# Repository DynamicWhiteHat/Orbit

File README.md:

# Orbit
## An ESP32-powered mini drone with autonomous following capability

## Features:
- ESP32 S3 Wroom 1u SoM
- 4x 0716 coreless motors
- MPU6050 for gyro
- QMC5883 compass
- MS5611 pressure sensor for altitude hold
- 3x SK6812 for signal LEDs
- Battery charging via USB-C
- 2x frame mounted DWM1000 for position tracking
- 1x small form factor DWM1000 board "beacon"
- Firmware based on flix by okalachev, modified to work with this project

## Why I designed this project:
I wanted to design a drone for HackClub's Blueprint program, but not just any regular drone. I wanted to add a feature that would make it stand out, something that would make it unique. So, I decided to give it the ability to autonomously follow you to an accurate degree. After doing some research, I found the DWM1000 modules and decided to design this project. I designed and redesigned the PCBs and CAD for this project many times, with each iteration improving upon the last. This project also gave me the ability to test and improve my PCB and CAD design skills. I understood a lot more about schematic connections while working on this project and learned to route much cleaner traces, even on a compact board.

## Image gallery:
<table align="center">
  <tr>
    <td align="center">
      
    </td>
    <td align="center">
      
    </td>
  </tr>
  <tr>
    <td align="center" colspan="2">
      
    </td>
  </tr>
</table>

## Schematics And PCBS

<details>
<summary>Drone Control Board</summary>
<table align="center">
  <tr>
    <td align="center" colspan="2">
      
    </td>
  </tr>
  <tr>
     <td align="center">
      
    </td>
    <td align="center">
      
    </td>
  </tr>
</table>
</details>

<details>
<summary>Beacon Board</summary>
<table align="center">
  <tr>
    <td align="center" colspan="2">
      
    </td>
  </tr>
  <tr>
     <td align="center">
      
    </td>
    <td align="center">
     
    </td>
  </tr>
</table>
</details>

<details>
<summary>UWB Module Board</summary>
<table align="center">
  <tr>
    <td align="center" colspan="2">
      
  </tr>
  <tr>
     <td align="center">
      
    </td>
    <td align="center">
      
    </td>
  </tr>
</table>
</details>

## How It Works

The drone is powered by a custom designed PCB based on the ESP-32 S3 Wroom 1u SoM. It includes three SK6812 mini-e LEDs to serve as a status signal, located at the rear of the drone. There are three sensors located on board to help with flight. The MPU-6050 is a triple-axis accelerometer and gyroscope that is essential to help the drone fly. The MS5611 is a pressure sensor that is used to record and maintain height during flight. The final sensor, an HMC5883, is a triple-axis magnetometer that is used to report the drone's heading. The latter two sensors are reported in QGroundControl or any other flight operating station to provide information to the controller. The 0716 coreless motors are powered by a simple MOSFET circuit, designed by MaxImagination. This circuit has a small footprint and fits great for small projects, such as this drone. Autonomous flight is achieved using two DWM1000 modules mounted on the sides of the drone. These were implemented on the main PCB using 10-pin JSTs to allow modular connectivity, allowing the controller to select whether to fly with or without the ranging sensors. The DWM1000s mounted on the drone communicate with an external DWM1000 "beacon" that is with the controller or person of interest. This beacon is encased in a watch case to make it easy to wear. By sending messages between the modules, the distance between them can be calculated, allowing the beacon's location to be triangulated. This location is then set in the PID controllers, allowing the drone to autonomously navigate.

## Bill Of Materials

| Item          | Description        | Quantity             | URL                                                                                 | Unit Price ($) | Total Price ($) |
|---------------|--------------------|----------------------|-------------------------------------------------------------------------------------|----------------|-----------------|
| DWM1000       | Ranging Modules    | 3                    | https://www.aliexpress.us/item/3256808347510093.html                                | $15.13         | $50.90          |
| XIAO ESP-32   | For Beacon         | 1                    | Already Have                                                                        |                |                 |
| LCSC          | PCB Components     | 1 Order of All Parts | See LCSC BOM                                                                        |                | $36.92          |
| JST Connector | For DWM Connection | 1 Pack of 10         | https://www.aliexpress.us/item/3256805775471278.html                                | $3.09          | $3.09           |
| Battery       | For Beacon         | 1                    | https://www.amazon.com/AKZYTUE-Battery-Rechargeable-Lithium-Connector/dp/B07TXJ4C46 | $7.79          | $7.79           |
| Battery       | For Drone          | 1                    | https://www.amazon.com/EEMB-Battery-Rechargeable-Lithium-Connector/dp/B0B7R8CS2C    | $6.99          | $7.99           |
| Motors        | For Drone          | 1 Pack of 4          | https://www.amazon.com/Coliao-Coreless-19000KV-Propeller-Quadcopter/dp/B0CHYDJMF2/  | $10            | $11             |
| Antenna       | For Drone          | 1                    | https://www.aliexpress.us/item/3256806233080373.html                                | $1.64          | $1.64           |
| Screws        | To Hold Case       | 1 Pack               | https://www.aliexpress.us/item/3256806233080373.html                                | $5.90          | $5.90           |
| JLCPCB Order  | PCBs               | 1                    | JLCPCB Quote                                                                        | $17.16          | $17.16           |
|               |                    |                      |                                                                                     |                | $139.08         |

### LCSC Bill Of Materials
| Description                                                                                 | Quantity Needed | Mrf#                    | Minimum Order Qty. | Unit Price(USD) | Ext.Price(USD) | LCSC#     | Product Link                                       |
|---------------------------------------------------------------------------------------------|-----------------|-------------------------|------------|-----------------|----------------|-----------|----------------------------------------------------|
| N-Channel 20V 4A 1.2W Surface Mount SOT-23                                                  | 4               | SI2300                  | 20         | 0.0164          | 0.33           | C5224175  | https://www.lcsc.com/product-detail/C5224175.html  |
| QFN-24-EP(4x4) Accelerometers RoHS                                                          | 1               | MPU-6050                | 1          | 6.8489          | 6.85           | C24112    | https://www.lcsc.com/product-detail/C24112.html    |
| 1Kpa~1.2bar QFN-8(3x5) Pressure Sensors, Transducers RoHS                                   | 1               | MS561101BA03-50         | 1          | 5.5485          | 5.55           | C15639    | https://www.lcsc.com/product-detail/C15639.html    |
| I2C LGA-16(3x3) Linear, Compass (ICs) RoHS                                                  | 1               | QMC5883P                | 1          | 1.4485          | 1.45           | C2847467  | https://www.lcsc.com/product-detail/C2847467.html  |
| Red LED Indication - Discrete 2.7V~3.2V 0602                                                | 5               | YLED0603R               | 200        | 0.0055          | 0.55           | C19171390 | https://www.lcsc.com/product-detail/C19171390.html |
| Emerald Green LED Indication - Discrete 2.7V~3.2V 0603                                      | 13             | YLED0603G               | 200        | 0.0054          | 1.08           | C19273151 | https://www.lcsc.com/product-detail/C19273151.html |
| 2.4GHz ESP32-S3R8 -98.2dBm SMD,19.2x18mm RF Transceiver Modules and Modems RoHS             | 1               | ESP32-S3-WROOM-1U-N16R8 | 1          | 5.3260          | 5.33           | C3013946  | https://www.lcsc.com/product-detail/C3013946.html  |
| 100nF ±10% 50V Ceramic Capacitor X7R 0603                                                   | 17              | CC0603KRX7R9BB104       | 100        | 0.0025          | 0.25           | C14663    | https://www.lcsc.com/product-detail/C14663.html    |
| 220nF ±10% 50V Ceramic Capacitor X7R 0603                                                   | 1               | CL10B224KB8NNNC         | 100        | 0.0081          | 0.81           | C64705    | https://www.lcsc.com/product-detail/C64705.html    |
| 4.7uF ±10% 10V Ceramic Capacitor X5R 0603                                                   | 3               | CL10A475KP8NNNC         | 50         | 0.0051          | 0.26           | C1705     | https://www.lcsc.com/product-detail/C1705.html     |
| 10uF ±10% 10V Ceramic Capacitor X5R 0603                                                    | 17              | CL10A106KP8NNNC         | 50         | 0.0058          | 0.29           | C19702    | https://www.lcsc.com/product-detail/C19702.html    |
| 1uF ±10% 50V Ceramic Capacitor X5R 0603                                                     | 1               | CL10A105KB8NNNC         | 50         | 0.0049          | 0.25           | C15849    | https://www.lcsc.com/product-detail/C15849.html    |
| 10nF ±10% 50V Ceramic Capacitor X7R 0603                                                    | 2               | CC0603KRX7R9BB103       | 100        | 0.0022          | 0.22           | C100042   | https://www.lcsc.com/product-detail/C100042.html   |
| Diode Independent 100V 300mA Surface Mount SOD-123                                          | 4               | 1N4148W                 | 100        | 0.0056          | 0.56           | C917030   | https://www.lcsc.com/product-detail/C917030.html   |
| Diode Array 1 Pair Common Cathode 30V 200mA Surface Mount SOT-23                            | 1               | BAT54C                  | 50         | 0.0063          | 0.32           | C916424   | https://www.lcsc.com/product-detail/C916424.html   |
| Diode 40V 1A Surface Mount SOD-123                                                          | 1               | 1N5819HW                | 20         | 0.0237          | 0.47           | C5439970  | https://www.lcsc.com/product-detail/C5439970.html  |
| USB-C (USB TYPE-C) Receptacle Connector 16 Position Surface Mount                           | 1               | TYPE-C-31-M-12          | 5          | 0.1762          | 0.88           | C165948   | https://www.lcsc.com/product-detail/C165948.html   |
| 100mW 10kΩ 75V ±100ppm/℃ Thick Film Resistor ±1% 0603 Chip Resistor - Surface Mount RoHS    | 14              | RC0603FR-0710KL         | 100        | 0.0011          | 0.11           | C98220    | https://www.lcsc.com/product-detail/C98220.html    |
| 5.1kΩ ±1% 100mW 0603 Thick Film Resistor                                                    | 2               | FRC0603F5101TS          | 100        | 0.0009          | 0.09           | C2907044  | https://www.lcsc.com/product-detail/C2907044.html  |
| 400mΩ ±1% 100mW 0603 Thick Film Resistor                                                    | 1               | FRL0603FR400TS          | 100        | 0.0033          | 0.33           | C5126047  | https://www.lcsc.com/product-detail/C5126047.html  |
| 1kΩ ±1% 100mW 0603 Thick Film Resistor                                                      | 10              | FRC0603F1001TS          | 100        | 0.0009          | 0.09           | C2907002  | https://www.lcsc.com/product-detail/C2907002.html  |
| 5kΩ 100mW 75V ±50ppm/℃ Thin Film Resistor ±0.1% 0603 Chip Resistor - Surface Mount RoHS     | 1               | RT0603BRE075KL          | 50         | 0.0172          | 0.86           | C862232   | https://www.lcsc.com/product-detail/C862232.html   |
| 100mW 1MΩ 75V ±100ppm/℃ Thick Film Resistor ±1% 0603 Chip Resistor - Surface Mount RoHS     | 5               | RC0603FR-071ML          | 100        | 0.0012          | 0.12           | C105578   | https://www.lcsc.com/product-detail/C105578.html   |
| Tactile Switch SPST 160gf 2mm SMD (SMT) Tab 4mm x 3mm Surface Mount                         | 2               | TS-1088-AR02016         | 10         | 0.0423          | 0.42           | C720477   | https://www.lcsc.com/product-detail/C720477.html   |
| Lithium Battery 1A ESOP-8 Battery Management RoHS                                           | 1               | TP4056-42-ESOP8         | 5          | 0.1784          | 0.89           | C16581    | https://www.lcsc.com/product-detail/C16581.html    |
| Positive Fixed 3.3V SOT-223 Voltage Regulators - Linear, Low Drop Out (LDO) Regulators RoHS | 5               | AP7361C-33E-13          | 5          | 0.2462          | 1.23           | C500795   | https://www.lcsc.com/product-detail/C500795.html   |
| 220kΩ ±1% 100mW 0603 Thick Film Resistor                                                    | 2               | FRC0603F2203TS          | 100        | 0.0010          | 0.10           | C2907013  | https://www.lcsc.com/product-detail/C2907013.html  |
| 470Ω ±1% 100mW 0603 Thick Film Resistor                                                     | 12              | 0603WAF4700T5E          | 100        | 0.0012          | 0.12           | C23179    | https://www.lcsc.com/product-detail/C23179.html    |
| Slide Switch SPDT 300mA @ 5V Surface Mount, Right Angle Rectangular Columnar                | 1               | SSSS811101              | 5          | 0.1408          | 0.70           | C109335   | https://www.lcsc.com/product-detail/C109335.html   |
| Connector Header 2 position 2mm Pitch 2A Right Angle -25℃~+85℃                            | 1               | S2B-PH-K-S(LF)(SN)      | 20         | 0.0351          | 0.70           | C17375    | https://lcsc.com/product-detail/C17375             |

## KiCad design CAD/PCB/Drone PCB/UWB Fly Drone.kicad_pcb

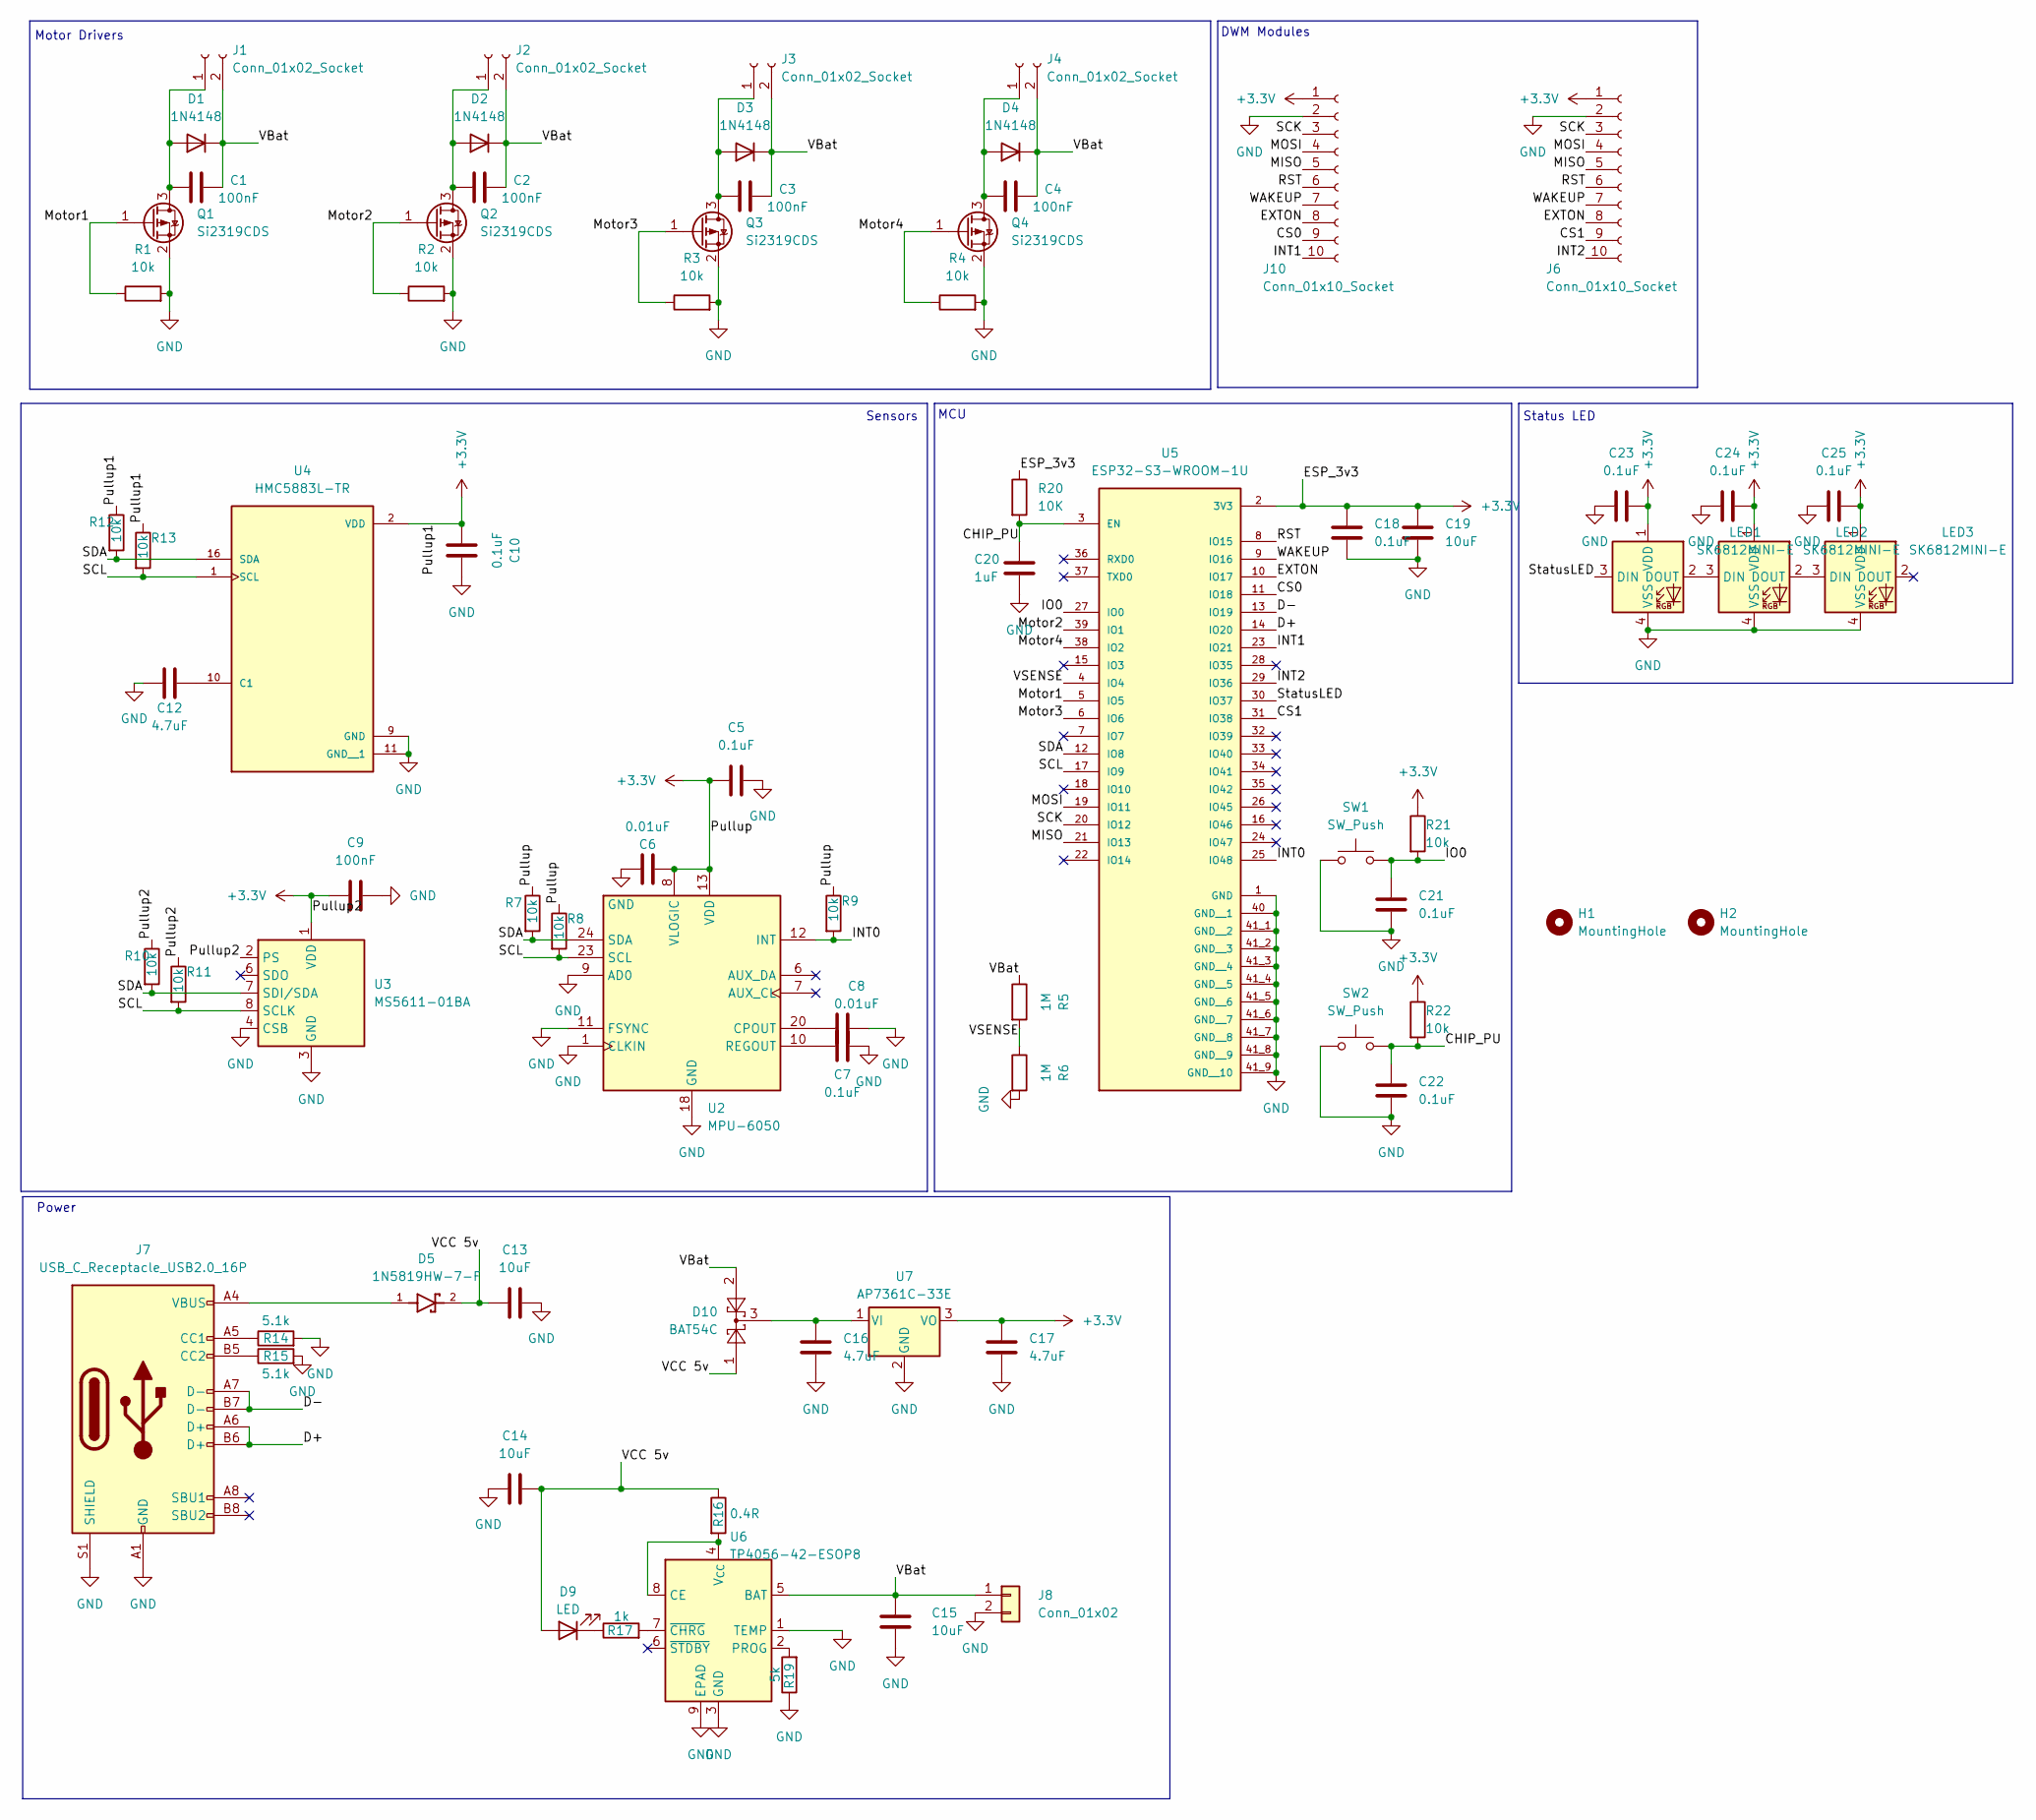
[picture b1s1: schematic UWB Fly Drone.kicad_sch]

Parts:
C1, C2, C3, C4, C9: 100nF; C_0603_1608Metric
C5, C7, C10, C18, C21, C22, C23, C24, C25: 0.1uF; C_0603_1608Metric
C6, C8: 0.01uF; C_0603_1608Metric
C12, C16, C17: 4.7uF; C_0603_1608Metric
C13, C14, C15, C19: 10uF; C_0603_1608Metric
C20: 1uF; C_0603_1608Metric
D1, D2, D3, D4: 1N4148; D_SOD-123
D5: 1N5819HW-7-F; D_SOD-123; PARTREV 18-2
D9: LED; LED_0603_1608Metric
D10: BAT54C; SOT-23
H1, H2: MountingHole; MountingHole_2.2mm_M2
J1, J2, J3, J4: Conn_01x02_Socket; SolderWire-0.5sqmm_1x02_P4.8mm_D0.9mm_OD2.3mm
J6, J10: Conn_01x10_Socket; JST_PH_S10B-PH-K_1x10_P2.00mm_Horizontal
J7: USB_C_Receptacle_USB2.0_16P; USB_C_Receptacle_HRO_TYPE-C-31-M-12
J8: Conn_01x02; JST_PH_S2B-PH-K_1x02_P2.00mm_Horizontal
LED1, LED2, LED3: SK6812MINI-E; LED_6028R
Q1, Q2, Q3, Q4: Si2319CDS; SOT-23
R1, R2, R3, R4, R7, R8, R9, R10, R11, R12, R13, R21, R22: 10k; R_0603_1608Metric
R5, R6: 1M; R_0603_1608Metric
R14, R15: 5.1k; R_0603_1608Metric
R16: 0.4R; R_0603_1608Metric
R17: 1k; R_0603_1608Metric
R19: 5k; R_0603_1608Metric
R20: 10K; R_0603_1608Metric
SW1, SW2: SW_Push; SW_TS-1088-AR02016
U2: MPU-6050; InvenSense_QFN-24_4x4mm_P0.5mm
U3: MS5611-01BA; LGA-8_3x5mm_P1.25mm
U4: HMC5883L-TR; XDCR_HMC5883L-TR; PARTREV E
U5: ESP32-S3-WROOM-1U; XCVR_ESP32-S3-WROOM-1U; PARTREV v0.6
U6: TP4056-42-ESOP8; SOIC-8-1EP_3.9x4.9mm_P1.27mm_EP2.41x3.3mm_ThermalVias
U7: AP7361C-33E; SOT-223-3_TabPin2

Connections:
+3.3V: C5.1, C6.1, C9.1, C10.1, C17.1, C18.1, C19.1, C23.2, C24.2, C25.2, J6.1, J10.1, LED1.1 (VDD), LED2.1 (VDD), LED3.1 (VDD), R7.1, R8.1, R9.1, R10.1, R11.1, R12.1, R13.1, R20.1, R21.1, R22.1, U2.8 (VLOGIC), U2.13 (VDD), U3.1 (VDD), U3.2 (PS), U4.2 (VDD), U5.2 (3V3), U7.3 (VO)
/CHIP_PU: C20.1, C22.1, R20.2, R22.2, SW2.2, U5.3 (EN)
/CS0: J10.9, U5.11 (IO18)
/CS1: J6.9, U5.31 (IO38)
/D+: J7.A6 (D+), J7.B6 (D+), U5.14 (IO20)
/D-: J7.A7 (D-), J7.B7 (D-), U5.13 (IO19)
/EXTON: J6.8, J10.8, U5.10 (IO17)
/INT0: R9.2, U2.12 (INT), U5.25 (IO48)
/INT1: J10.10, U5.23 (IO21)
/INT2: J6.10, U5.29 (IO36)
/IO0: C21.1, R21.2, SW1.2, U5.27 (IO0)
/MISO: J6.5, J10.5, U5.21 (IO13)
/MOSI: J6.4, J10.4, U5.19 (IO11)
/Motor1: Q1.1 (G), R1.1, U5.5 (IO5)
/Motor2: Q2.1 (G), R2.1, U5.39 (IO1)
/Motor3: Q3.1 (G), R3.1, U5.6 (IO6)
/Motor4: Q4.1 (G), R4.1, U5.38 (IO2)
/RST: J6.6, J10.6, U5.8 (IO15)
/SCK: J6.3, J10.3, U5.20 (IO12)
/SCL: R8.2, R11.2, R13.2, U2.23 (SCL), U3.8 (SCLK), U4.1 (SCL), U5.17 (IO9)
/SDA: R7.2, R10.2, R12.2, U2.24 (SDA), U3.7 (SDI/SDA), U4.16 (SDA), U5.12 (IO8)
/StatusLED: LED1.3 (DIN), U5.30 (IO37)
/VBat: C1.2, C2.2, C3.2, C4.2, C15.1, D1.1 (K), D2.1 (K), D3.1 (K), D4.1 (K), D10.2, J1.2, J2.2, J3.2, J4.2, J8.1, R5.1, U6.5 (BAT)
/VCC 5v: C13.1, C14.2, D5.2, D9.2 (A), D10.1, R16.1
/VSENSE: R5.2, R6.1, U5.4 (IO4)
/WAKEUP: J6.7, J10.7, U5.9 (IO16)
GND: C5.2, C6.2, C7.2, C8.2, C9.2, C10.2, C12.1, C13.2, C14.1, C15.2, C16.2, C17.2, C18.2, C19.2, C20.2, C21.2, C22.2, C23.1, C24.1, C25.1, J6.2, J7.A1 (GND), J7.A12 (GND), J7.B1 (GND), J7.B12 (GND), J7.S1 (SHIELD), J8.2, J10.2, LED1.4 (VSS), LED2.4 (VSS), LED3.4 (VSS), Q1.2 (S), Q2.2 (S), Q3.2 (S), Q4.2 (S), R1.2, R2.2, R3.2, R4.2, R6.2, R14.2, R15.2, R19.1, SW1.1, SW2.1, U2.1 (CLKIN), U2.9 (AD0), U2.11 (FSYNC), U2.18 (GND), U3.3 (GND), U3.4 (CSB), U3.5 (CSB), U4.9 (GND), U4.11 (GND__1), U5.1 (GND), U5.40 (GND__1), U5.41_1 (GND__2), U5.41_2 (GND__3), U5.41_3 (GND__4), U5.41_4 (GND__5), U5.41_5 (GND__6), U5.41_6 (GND__7), U5.41_7 (GND__8), U5.41_8 (GND__9), U5.41_9 (GND__10), U6.1 (TEMP), U6.3 (GND), U6.9 (EPAD), U7.2 (GND)
unnamed: C1.1, D1.2 (A), J1.1, Q1.3 (D)
unnamed: C2.1, D2.2 (A), J2.1, Q2.3 (D)
unnamed: C3.1, D3.2 (A), J3.1, Q3.3 (D)
unnamed: C4.1, D4.2 (A), J4.1, Q4.3 (D)
unnamed: D5.1, J7.A4 (VBUS), J7.A9 (VBUS), J7.B4 (VBUS), J7.B9 (VBUS)
unnamed: D9.1 (K), R17.1
unnamed: J7.A5 (CC1), R14.1
unnamed: J7.B5 (CC2), R15.1
unnamed: LED1.2 (DOUT), LED2.3 (DIN)
unnamed: LED2.2 (DOUT), LED3.3 (DIN)
unnamed: C8.1, U2.20 (CPOUT)
unnamed: C7.1, U2.10 (REGOUT)
unnamed: C12.2, U4.10 (C1)
unnamed: R16.2, U6.4 (V_{CC}), U6.8 (CE)
unnamed: R19.2, U6.2 (PROG)
unnamed: R17.2, U6.7 (~CHRG)
unnamed: C16.1, D10.3, U7.1 (VI)

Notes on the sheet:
Status LED
MCU
Motor Drivers
DWM Modules
Power
Sensors

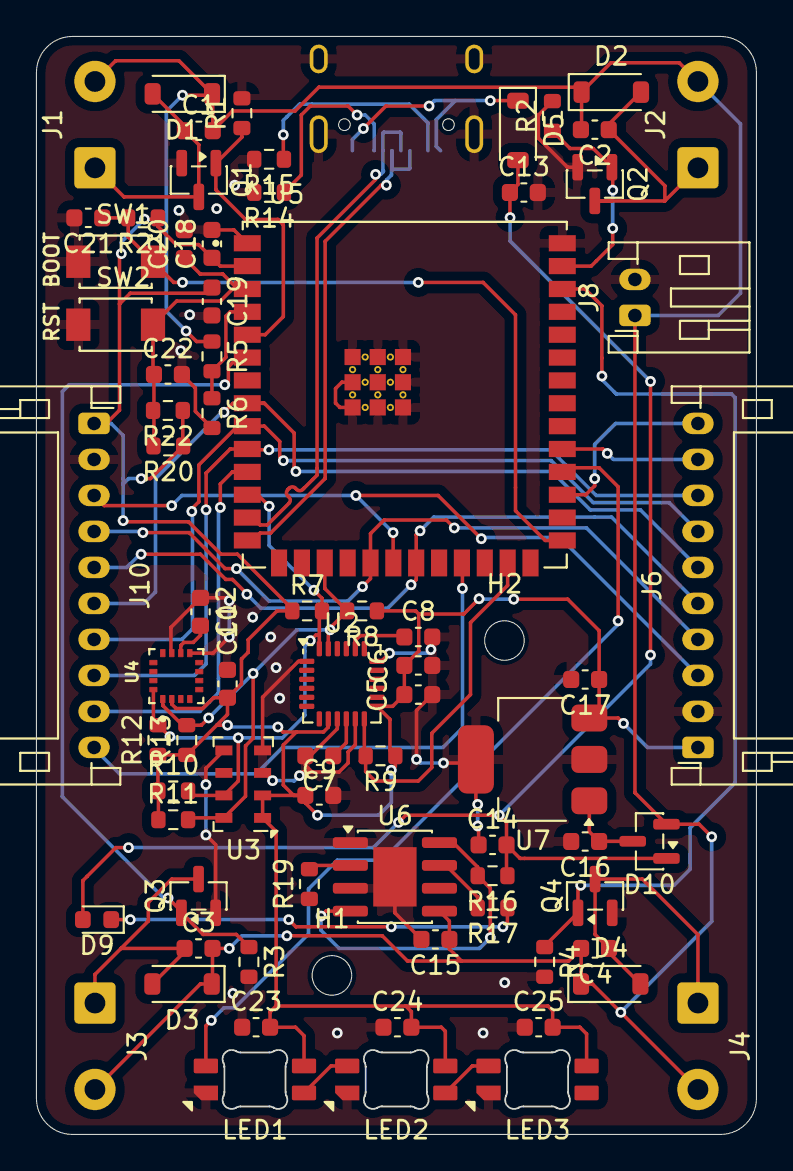
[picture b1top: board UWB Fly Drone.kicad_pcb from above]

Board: 2 copper layers, 39.9 x 61.0 mm, 77 parts (1 on the bottom side), 44 nets.

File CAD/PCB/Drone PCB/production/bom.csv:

Designator,Footprint,Quantity,Value,LCSC Part #
"C1, C2, C3, C4, C9",0603,5,100nF,
"C10, C18, C21, C22, C23, C24, C25, C5, C7",0603,9,0.1uF,
"C12, C16, C17",0603,3,4.7uF,
"C13, C14, C15, C19",0603,4,10uF,
C20,0603,1,1uF,
"C6, C8",0603,2,0.01uF,
"D1, D2, D3, D4",D_SOD-123,4,1N4148,
D10,SOT-23,1,BAT54C,
D5,D_SOD-123,1,1N5819HW-7-F,
D9,0603,1,LED,
"J1, J2, J3, J4",SolderWire-0.5sqmm_1x02_P4.8mm_D0.9mm_OD2.3mm,4,Conn_01x02_Socket,
"J10, J6",JST_PH_S10B-PH-K_1x10_P2.00mm_Horizontal,2,Conn_01x10_Socket,
J7,USB_C_Receptacle_HRO_TYPE-C-31-M-12,1,USB_C_Receptacle_USB2.0_16P,
J8,JST_PH_S2B-PH-K_1x02_P2.00mm_Horizontal,1,Conn_01x02,
"LED1, LED2, LED3",LED_6028R,3,SK6812MINI-E,
"Q1, Q2, Q3, Q4",SOT-23,4,Si2319CDS,
"R1, R10, R11, R12, R13, R2, R20, R21, R22, R3, R4, R7, R8, R9",0603,14,10k,
"R14, R15",0603,2,5.1k,
R16,0603,1,0.4R,
R17,0603,1,1k,
R19,0603,1,5k,
"R5, R6",0603,2,1M,
"SW1, SW2",SW_TS-1088-AR02016,2,SW_Push,
U2,InvenSense_QFN-24_4x4mm_P0.5mm,1,MPU-6050,
U3,LGA-8_3x5mm_P1.25mm,1,MS5611-01BA,
U4,XDCR_HMC5883L-TR,1,HMC5883L-TR,
U5,XCVR_ESP32-S3-WROOM-1U,1,ESP32-S3-WROOM-1U,
U6,SOIC-8-1EP_3.9x4.9mm_P1.27mm_EP2.41x3.3mm_ThermalVias,1,TP4056-42-ESOP8,
U7,SOT-223-3_TabPin2,1,AP7361C-33E,

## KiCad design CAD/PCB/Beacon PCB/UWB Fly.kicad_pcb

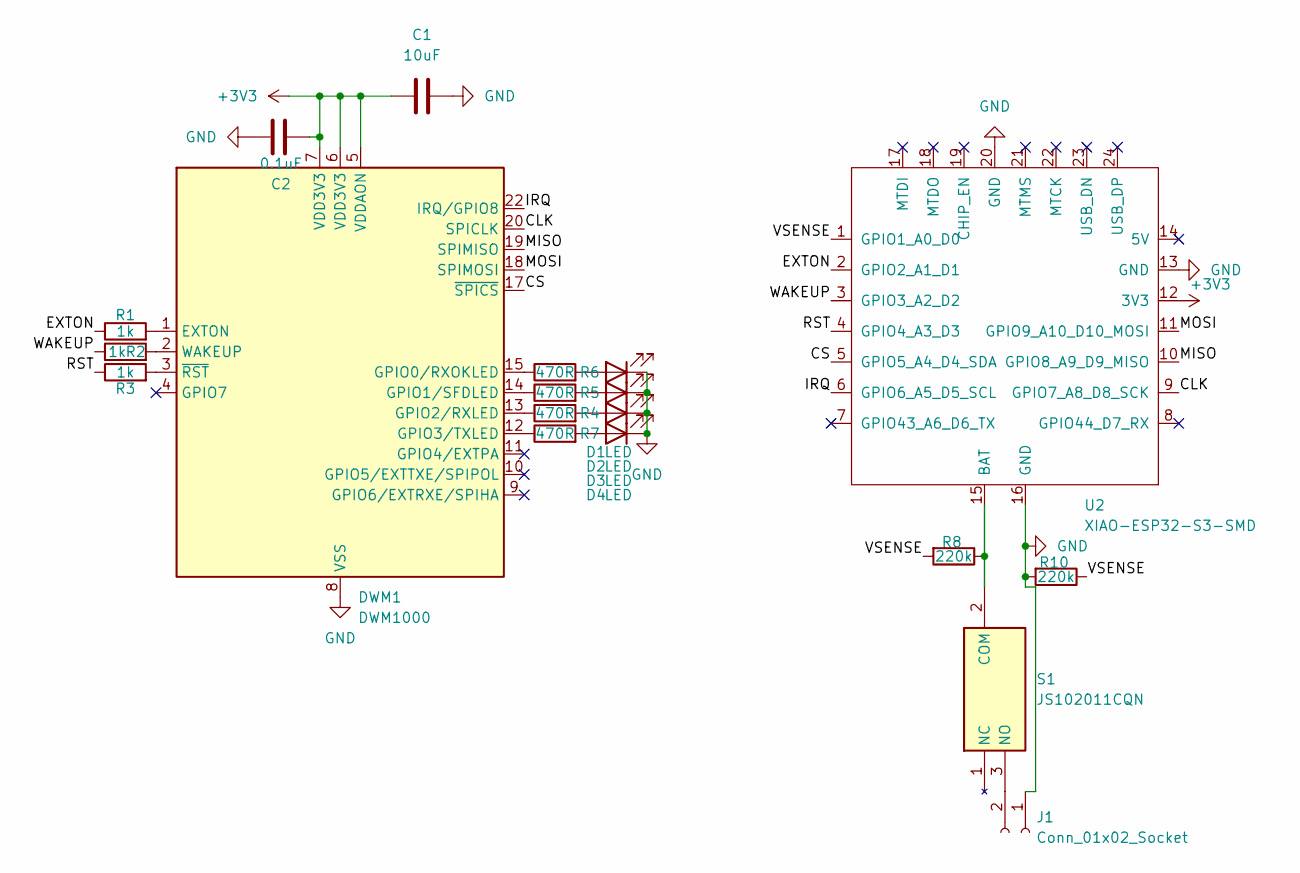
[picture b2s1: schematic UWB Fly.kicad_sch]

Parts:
C1: 10uF; C_0603_1608Metric
C2: 0.1uF; C_0603_1608Metric
D1, D2, D3, D4: LED; LED_0603_1608Metric
DWM1: DWM1000
J1: Conn_01x02_Socket; SolderWire-0.5sqmm_1x02_P4.8mm_D0.9mm_OD2.3mm
R1, R2, R3: 1k; R_0603_1608Metric
R4, R5, R6, R7: 470R; R_0603_1608Metric
R8, R10: 220k; R_0603_1608Metric
S1: JS102011CQN; SW_SSSS811101; Mouser Part Number 611-JS102011CQN
U2: XIAO-ESP32-S3-SMD; XIAO-ESP32S3-SMD

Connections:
+3V3: C1.1, C2.1, DWM1.5 (VDDAON), DWM1.6 (VDD3V3), DWM1.7 (VDD3V3), U2.12 (3V3)
/CLK: DWM1.20 (SPICLK), U2.9 (GPIO7_A8_D8_SCK)
/CS: DWM1.17 (~SPICS), U2.5 (GPIO5_A4_D4_SDA)
/EXTON: R1.1, U2.2 (GPIO2_A1_D1)
/IRQ: DWM1.22 (IRQ/GPIO8), U2.6 (GPIO6_A5_D5_SCL)
/MISO: DWM1.19 (SPIMISO), U2.10 (GPIO8_A9_D9_MISO)
/MOSI: DWM1.18 (SPIMOSI), U2.11 (GPIO9_A10_D10_MOSI)
/RST: R3.1, U2.4 (GPIO4_A3_D3)
/VSENSE: R8.2, R10.1, U2.1 (GPIO1_A0_D0)
/WAKEUP: R2.1, U2.3 (GPIO3_A2_D2)
GND: C1.2, C2.2, D1.1 (K), D2.1 (K), D3.1 (K), D4.1 (K), DWM1.8 (VSS), DWM1.16 (VSS), DWM1.21 (VSS), DWM1.23 (VSS), DWM1.24 (VSS), J1.1, R10.2, U2.13 (GND), U2.16 (GND), U2.20 (GND)
unnamed: D1.2 (A), R6.2
unnamed: D2.2 (A), R5.2
unnamed: D3.2 (A), R4.2
unnamed: D4.2 (A), R7.2
unnamed: DWM1.1 (EXTON), R1.2
unnamed: DWM1.15 (GPIO0/RXOKLED), R6.1
unnamed: DWM1.14 (GPIO1/SFDLED), R5.1
unnamed: DWM1.13 (GPIO2/RXLED), R4.1
unnamed: DWM1.12 (GPIO3/TXLED), R7.1
unnamed: DWM1.2 (WAKEUP), R2.2
unnamed: DWM1.3 (~RST), R3.2
unnamed: J1.2, S1.3 (NO)
unnamed: R8.1, S1.2 (COM), U2.15 (BAT)

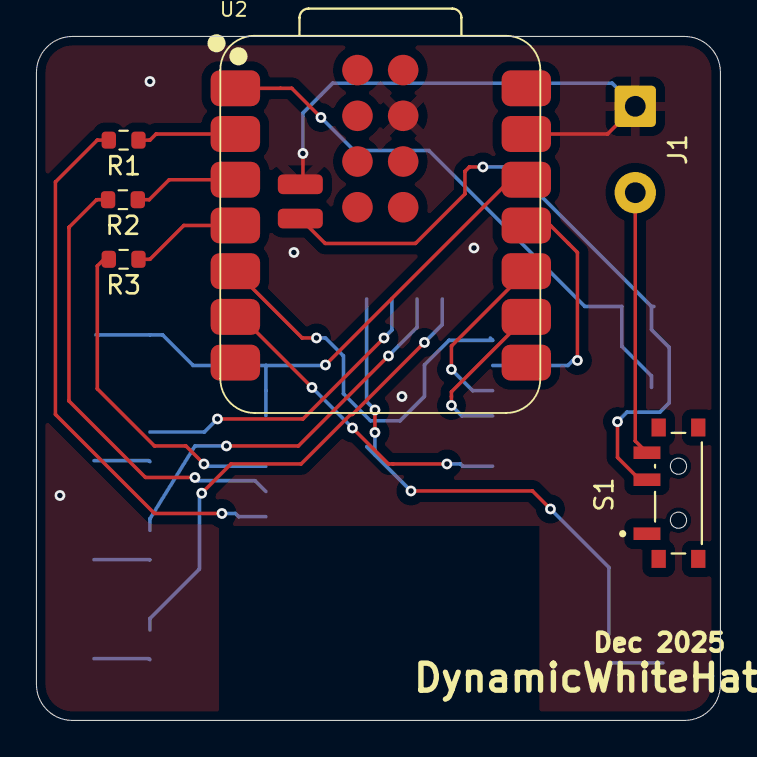
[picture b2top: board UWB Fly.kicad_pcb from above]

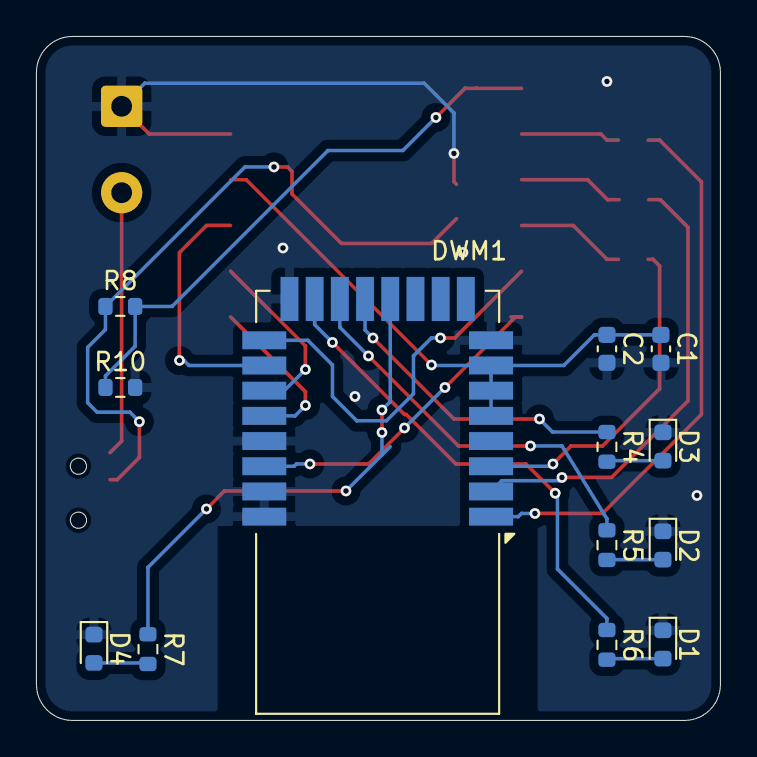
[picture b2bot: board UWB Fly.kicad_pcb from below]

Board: 2 copper layers, 38.0 x 38.0 mm, 19 parts (13 on the bottom side), 24 nets.

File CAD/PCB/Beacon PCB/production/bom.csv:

Designator,Footprint,Quantity,Value,LCSC Part #
C1,0603,1,10uF,
C2,0603,1,0.1uF,
"D1, D2, D3, D4",0603,4,LED,
DWM1,DWM1000,1,DWM1000,
J1,SolderWire-0.5sqmm_1x02_P4.8mm_D0.9mm_OD2.3mm,1,Conn_01x02_Socket,
"R1, R2, R3",0603,3,1k,
"R10, R8",0603,2,220k,
"R4, R5, R6, R7",0603,4,470R,
S1,SW_SSSS811101,1,JS102011CQN,
U2,XIAO-ESP32S3-SMD,1,XIAO-ESP32-S3-SMD,

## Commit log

2025-12-29 Add project title and description to README
2025-12-29 Revise README for Orbit drone project
    Updated project name and added detailed features and design rationale.
2025-12-29 Fix duplicate text in README project description
    Removed duplicate text in project description.
2025-12-29 Enhance README with image gallery and BOM
    Added image gallery and Bill of Materials sections to README.
2025-12-29 Adjust component prices in README
    Updated prices for various components in the BOM.
2025-12-29 Fix battery price for drone in README
    Updated the price of the battery for the drone.
2025-12-29 Update BOM with new items and pricing
    Added JLCPCB Order to the BOM and updated prices.
2025-12-29 Update Bill Of Materials with new entries
    Added JLCPCB order for PCBs and updated total prices.
2025-12-29 Update project rationale in README.md
    Refine project description and enhance clarity.
2025-12-29 Added STEP
2025-12-29 Mention use of ESP-Drone firmware in README
    Added a note about using pre-existing ESP-Drone firmware.
2025-12-29 Adjust JLCPCB order cost in README
    Updated JLCPCB order cost and total price in the BOM.
2025-12-29 Revise BOM with new items and price updates
    Updated the BOM with new items and adjusted prices.
2025-12-29 Add Hot Plate to BOM in README
    Added Hot Plate to the soldering materials list with pricing.
2025-12-29 Update BOM with new items and total prices
    Added new items to the BOM including a Hot Plate and updated total prices.
2025-12-30 Update README with firmware information
    Added firmware details and source link to README.
2025-12-30 Revise BOM with updated items and prices
    Updated item list and quantities in the BOM.
2025-12-30 Revise Orbit BOM with new components and prices
    Updated item list with new entries and corrected quantities.
2025-12-30 Update Orbit BOM with new items and prices
2025-12-30 Added firmware
2025-12-30 Removed firmware
2025-12-30 Added back firmware
2025-12-30 Remove firmware section from README
    Removed firmware section that described its features and link.
2025-12-30 Add schematics and PCB details to README
    Added schematics and PCB details for Drone Control Board, Beacon Board, and UWB Module Board.
2026-01-02 Fix typo in MaxImagionation to MaxImagination
2026-01-04 Update BOM by removing Hot Plate and adjusting total
    Removed 'Hot Plate' entry and updated total cost.
2026-01-04 Revise BOM with updated items and pricing
    Updated item list and prices in the BOM.
2026-01-04 Update JLCPCB order cost in README
2026-01-04 Revise quantities and prices in Orbit BOM
    Updated item quantities and prices in the BOM.
2026-01-05 Removed solder paste
2026-01-05 Update item list in Orbit BOM CSV
2026-01-06 Update README with firmware details
    Added information about firmware used in the project.
